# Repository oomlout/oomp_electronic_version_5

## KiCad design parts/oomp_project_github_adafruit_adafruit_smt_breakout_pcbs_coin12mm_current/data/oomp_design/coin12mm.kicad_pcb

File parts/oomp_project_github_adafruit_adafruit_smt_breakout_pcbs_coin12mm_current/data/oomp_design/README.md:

# OOMP KiCad design copy

Open `coin12mm.kicad_pro` (or the `.kicad_pcb` / `.kicad_sch`) in KiCad. Local OOMP libraries are under `libraries/`. Original inputs are preserved in [../original/](../original/).

Only verified unchanged installed KiCad defaults were renamed. Modified, custom, unmatched and unavailable items remain unchanged. Soldering variants are never swapped during conversion. Existing pad coordinates, nets and UUIDs are preserved.

See [conversion_report.yaml](conversion_report.yaml) for every conversion and skip. Copy this directory before editing; regeneration refuses to overwrite edited design files.

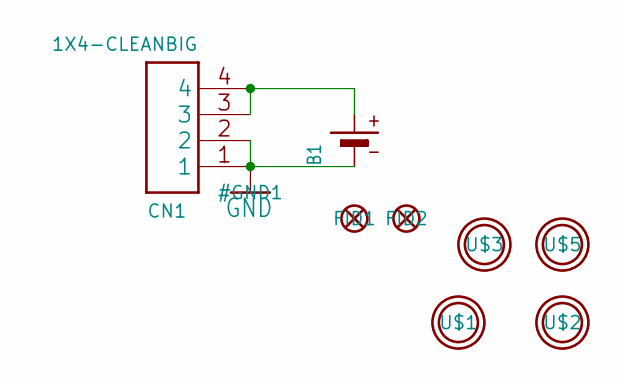
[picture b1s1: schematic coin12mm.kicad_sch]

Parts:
B1: BATTERYCR1220_SMT; CR1220
CN1: 1X4-CLEANBIG; 1X04-CLEANBIG
FID1, FID2: FIDUCIAL""; FIDUCIAL_1MM
U$1, U$2, U$3, U$5: MOUNTINGHOLE2.5; MOUNTINGHOLE_2.5_PLATED

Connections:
GND: B1.-, CN1.1, CN1.2
unnamed: B1.+$1 (+), CN1.3, CN1.4

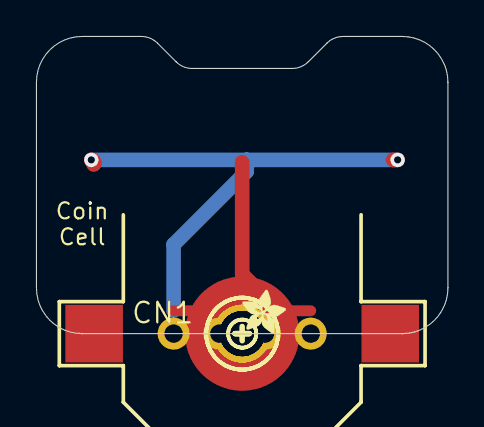
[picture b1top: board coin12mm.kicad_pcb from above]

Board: 2 copper layers, 22.9 x 16.5 mm, 12 parts (1 on the bottom side), 2 nets.

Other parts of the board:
U$4: ADAFRUIT_5MM
U$6: SYMBOL_PLUS
U$7: SYMBOL_MINUS
U$8: ADAFRUIT_2.5MM
